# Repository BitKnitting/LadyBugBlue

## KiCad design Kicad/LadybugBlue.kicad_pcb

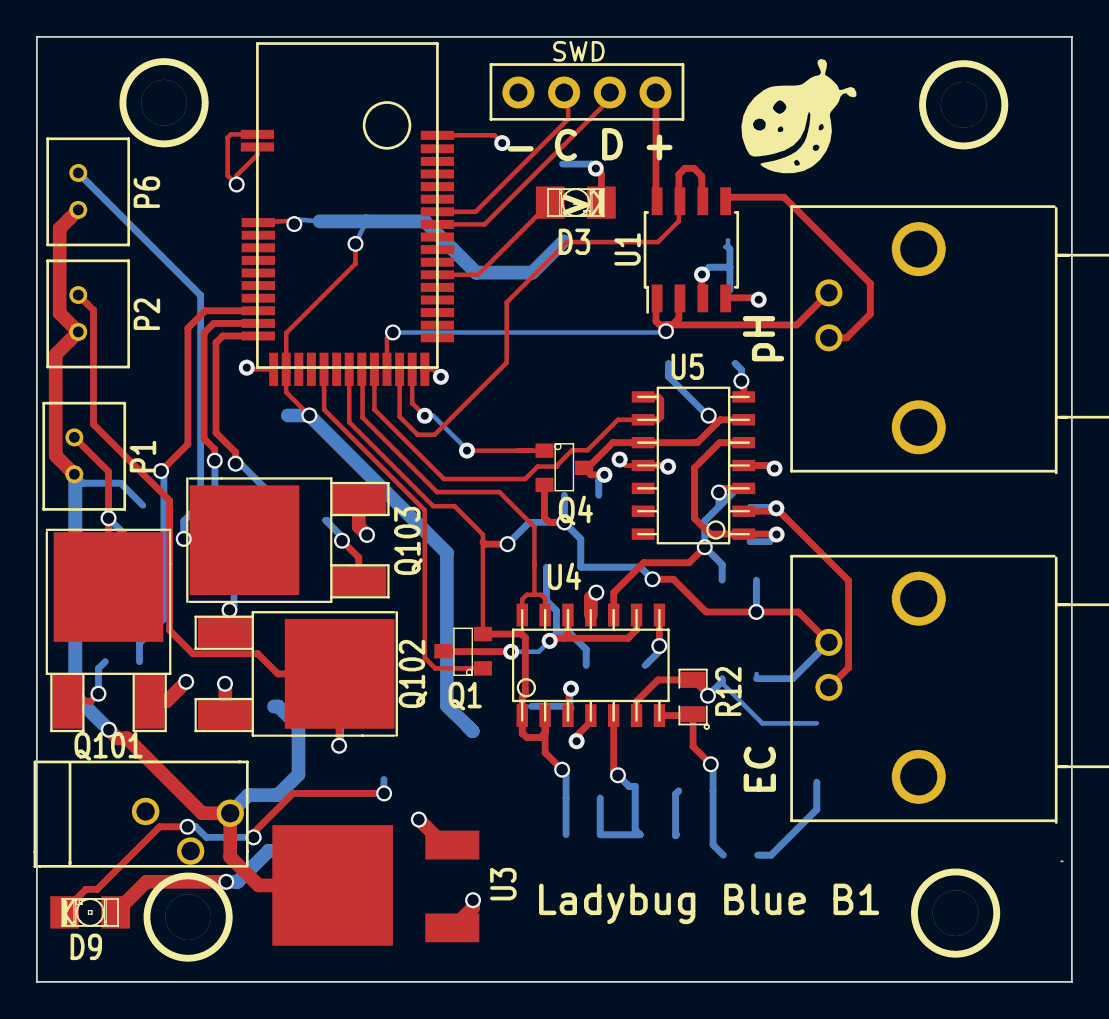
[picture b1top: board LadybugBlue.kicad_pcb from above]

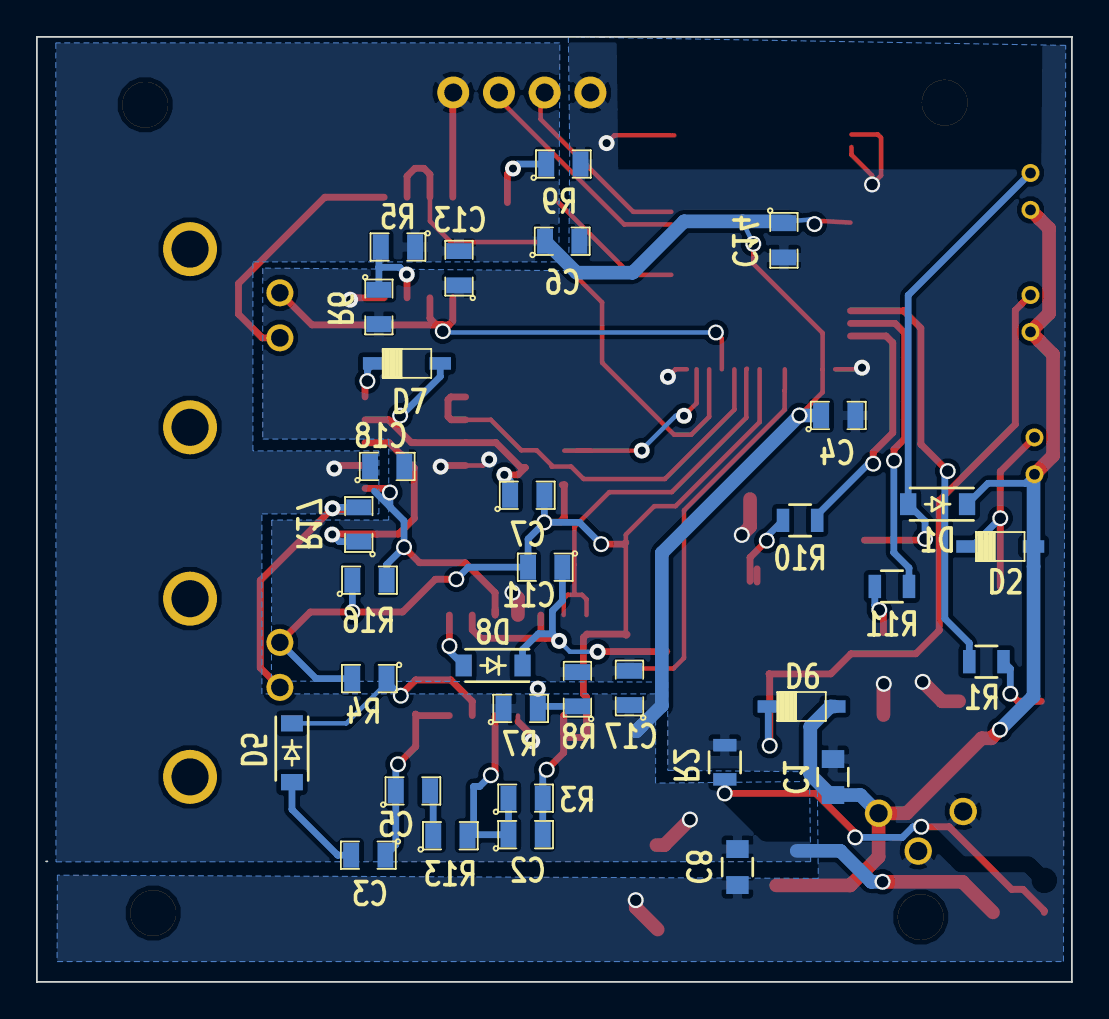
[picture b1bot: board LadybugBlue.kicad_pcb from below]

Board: 2 copper layers, 57.5 x 52.5 mm, 53 parts (33 on the bottom side), 39 nets.

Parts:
C1: .1u; C_0805
C2, C3, C4, C5, C6, C7, C11, C13, C17, C18: .1u; SM0805
C8: 10u; C_0805
C14: 1u; SM0805
CON1: BARREL_JACK; LB_BarrelJack
D1, D2, D5, D6, D7, D8: D; SOD-123
D3, D9: LED; LB_LED-1206
P1, P2, P6: CONN_01X02; PH_CONN_2_POS
P3: SWD; LB_SWD
P4, P5: BNC; LB_BNC
Q1, Q4: LB_MOSFET_N; LB_MOSFET
Q101, Q102, Q103: TIP122; DPAK2
R1, R10, R11: 2.2K; R_0805
R2: 330; R_0805
R3, R5, R6, R7, R8, R9, R13: 1K; SM0805
R4, R16: 10K; SM0805
R12: 22K; SM0805
R17: 1K .5%; SM0805
U1: MCP6242; SOIC-8_3.9x4.9mm_Pitch1.27mm
U2: MDBT40; LB_MDBT40
U3: LD1117; DPAK
U4, U5: MCP6244; LB_MCP6244

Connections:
/Pumps/pump1: D2.2, P1.2, Q101.2
/Pumps/pump1_pin: R1.1, U2.10
/Pumps/pump2: D6.2, P2.2, Q102.2
/Pumps/pump2_pin: R11.1, U2.11
/Pumps/pump3: D1.2, P6.2, Q103.2
/Pumps/pump3_pin: R10.1, U2.12
/nRF51822/BLE LED: D3.1, U2.31
/nRF51822/EC_VIN_AIN: U2.20, U4.13, U4.14
/nRF51822/EC_VOUT_AIN: U2.21, U5.8, U5.9
/nRF51822/FET_VIN_pin: Q1.G, U2.17
/nRF51822/FET_VOUT_pin: Q4.G, U2.24
/nRF51822/SWCLK: P3.3, U2.36
/nRF51822/SWD: P3.2, U2.35
/nRF51822/VGND_EC: C2.2, C7.2, C11.2, P5.2, Q1.S, Q4.S, R3.2, R4.2, R16.1, U2.19, U4.1, U4.2
/nRF51822/VGND_pH: P4.2, U1.1, U1.2, U2.22
/nRF51822/pH_AIN: U1.6, U1.7, U2.23
/sensors/EC/AC/G1: C3.2, D5.2
/sensors/EC/AC/W_Vin+: C2.1, R3.1, R13.2, U4.5
/sensors/EC/AC/W_Vin-: D5.1, R4.1, R12.2, U4.6
/sensors/EC/AC/W_Vout: C3.1, C5.1, R12.1, U4.7
/sensors/EC/AC/f1: C5.2, R13.1
/sensors/EC/Rectify/EC_VIN: R16.2, U4.10, U5.3
/sensors/EC/Rectify/R_VIN_-: C11.1, D8.1, Q1.D, U4.9, U4.12
/sensors/EC/Rectify/R_VIN_out: D8.2, U4.8
/sensors/EC/Rectify_VOUT/EC_VOUT: R17.1, U5.1, U5.5
/sensors/EC/Rectify_VOUT/R_VOUT_-: C7.1, D7.1, Q4.D, U5.6, U5.10
/sensors/EC/Rectify_VOUT/R_VOUT_OUT: D7.2, U5.7
/sensors/EC_ProbeIN: P5.1, R17.2, U5.2
/sensors/pH_ProbeIN: P4.1, U1.5
GND: C1.2, C4.2, C6.2, C8.2, C13.1, C14.2, C17.2, C18.2, CON1.2, CON1.3, P3.4, Q101.3, Q102.3, Q103.3, R2.1, R6.2, R8.2, R9.2, U1.4, U2.1, U2.2, U2.13, U2.25, U2.42, U3.1, U4.11, U5.11
unnamed: D3.2, R9.1
unnamed: D9.2, R2.2
unnamed: Q101.1, R1.2
unnamed: Q102.1, R11.2
unnamed: Q103.1, R10.2
unnamed: R5.2, R6.1, U1.3
unnamed: R7.2, R8.1, U4.3
pumpPWR: C1.1, CON1.1, D1.1, D2.1, D6.1, P1.1, P2.1, P6.1, U3.2
µPWR: C4.1, C6.1, C8.1, C13.2, C14.1, C17.1, C18.1, D9.1, P3.1, R5.1, R7.1, U1.8, U2.3, U2.14, U3.3, U4.4, U5.4

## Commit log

2015-07-23 adding ble_app_template Eclipse project
2015-07-23 updated ble_template.zip Eclipse project file to include SEGGER debugging commands/info
2015-07-23 added ble_timer_template.zip Eclipse project - adds a timer to the ble_template example
2015-07-25 added ADS1015 Eclipse project and breadboard drawing of test EC Circuit
2015-07-29 added ADC_simple Eclipse project
2015-07-31 added blinkyBlueFruit.zip Eclipse project to test external debugging
2015-08-01 updated blinkyBlueFruit
2015-08-01 updated a comment in blinkyBlueFruit
2015-08-16 added keepIt100_ADC_simple
2015-08-23 added app_timer test as example of using the app_timer APIs which sit on top of RTC1
2015-08-23 updated app_timerTest Eclipse example to use 1 RTC queue/timer
2015-08-23 cosmetic changes to app_timerTest Eclipse example
2015-08-23 added BatteryLevelCheck Eclipse example
2015-09-06 added Blinky_ManagedMake_1.zip
2016-02-25 significant update to schematic and layout
2016-02-25 updated layout
2016-02-25 cleaned up layout and added python script
2016-02-25 minor update of python script
